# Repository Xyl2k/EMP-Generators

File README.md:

EMP-Generators
==============

Eagle schematics for various basic EMP Generators.

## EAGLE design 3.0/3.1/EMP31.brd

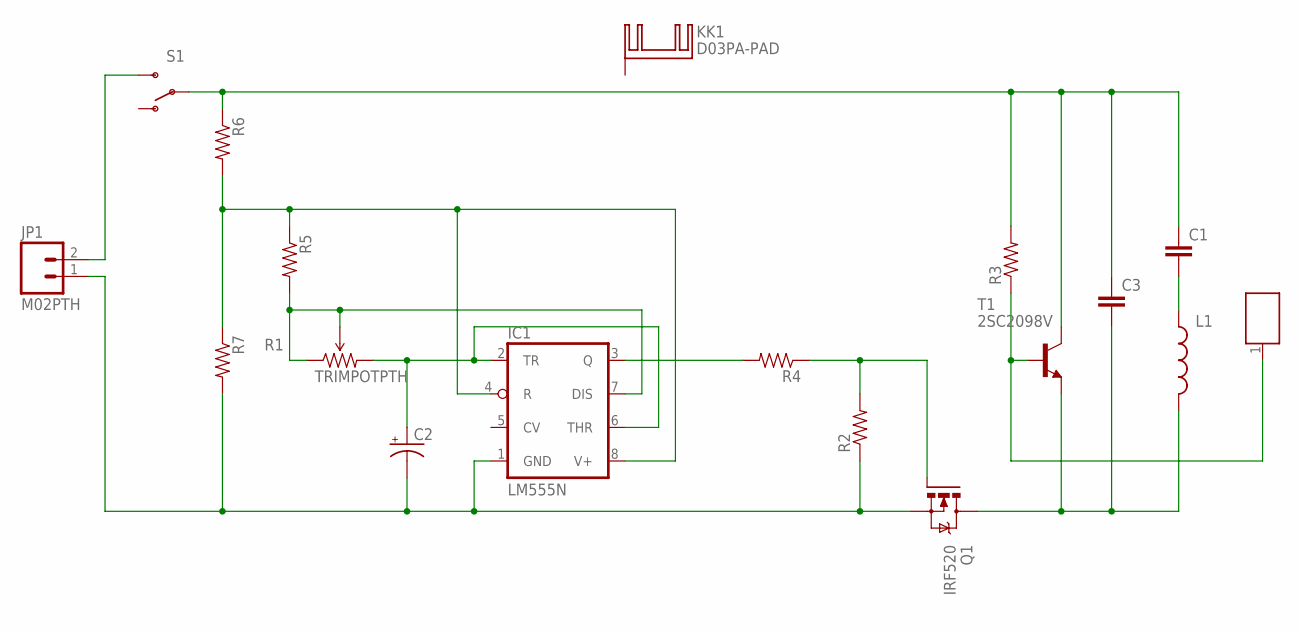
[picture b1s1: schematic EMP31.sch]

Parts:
C1, C3: CAPEZ; CAP-PTH-SMALLEZ
C2: CAP_POLPTH2; CPOL-RADIAL-10UF-25V
IC1: LM555N; DIL08-ROUND
JP1: M02PTH; 1X02
KK1: D03PA-PAD
L1: INDUCTORCR54-KIT; CR54-KIT
Q1: IRF520; TO220BV
R1: TRIMPOTPTH; TRIM_POT_PTH
R2, R3, R4, R5, R6, R7: RESISTOREZ; AXIAL-0.3EZ
S1: SWITCH-SPDTPTH; SWITCH-SPDT
T1: 2SC2098V; TO220AV
U$1: L2_JOB37

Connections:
GND: C2.2 (-), IC1.1 (GND), JP1.1, Q1.S, R2.P$1 (1), R7.P$2 (2)
unnamed: C1.2, L1.P$1 (1)
unnamed: R3.P$1 (1), T1.1 (B), U$1.1
unnamed: C3.2, L1.P$2 (2), Q1.D, T1.3 (E)
unnamed: Q1.G, R2.P$2 (2), R4.P$1 (1)
unnamed: IC1.3 (Q), R4.P$2 (2)
unnamed: C2.1 (+), IC1.2 (TR), IC1.6 (THR), R1.3 (CW)
unnamed: IC1.7 (DIS), R1.1 (CCW), R1.2 (WIPER), R5.P$2 (2)
unnamed: IC1.4 (R), IC1.8 (V+), R5.P$1 (1), R6.P$2 (2), R7.P$1 (1)
unnamed: C1.1, C3.1, R3.P$2 (2), R6.P$1 (1), S1.2, T1.2 (C)
unnamed: JP1.2, S1.3 (S)

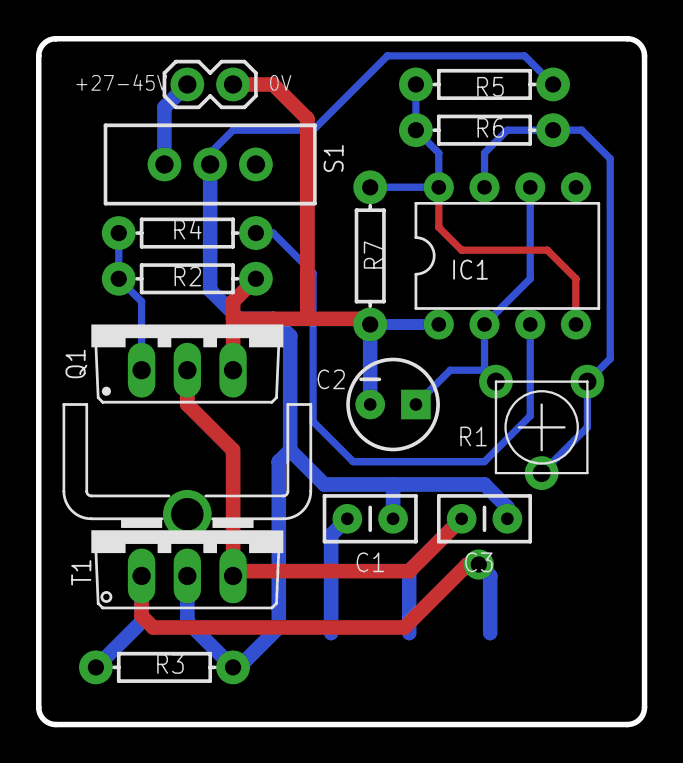
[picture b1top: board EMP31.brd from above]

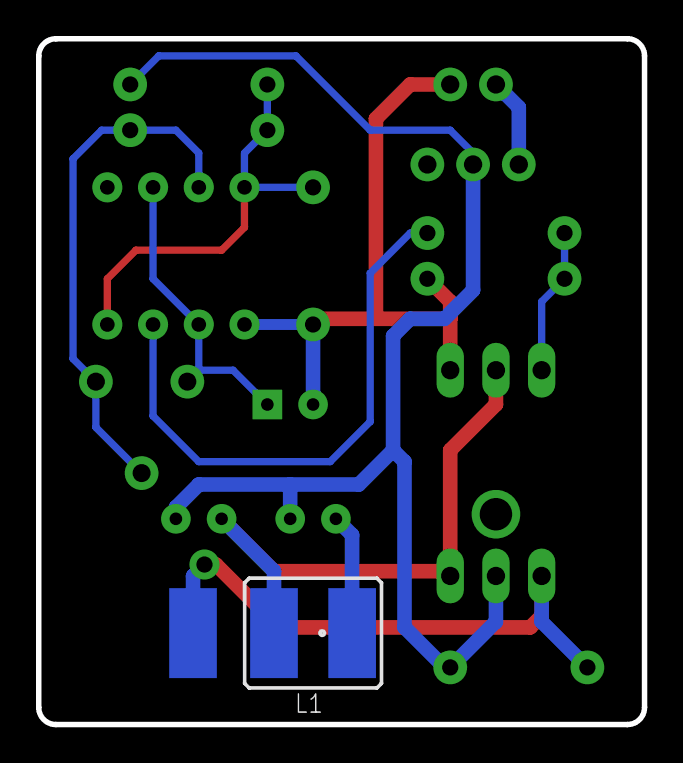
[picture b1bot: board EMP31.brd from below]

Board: 2 copper layers, 33.7 x 38.1 mm, 18 parts (2 on the bottom side), 11 nets.

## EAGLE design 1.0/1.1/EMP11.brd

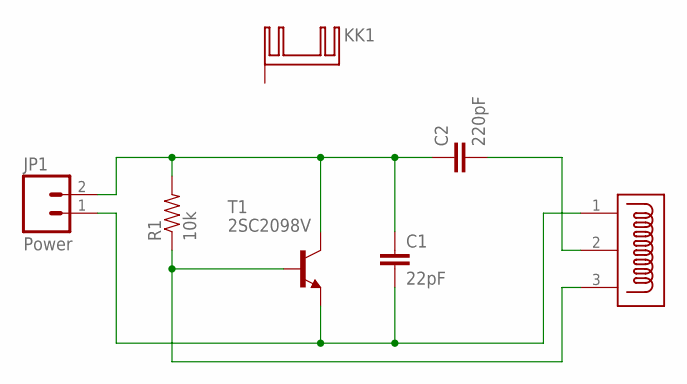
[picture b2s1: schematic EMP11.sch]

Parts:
C1: 22pF; CAP-PTH-SMALL
C2: 220pF; CAP-PTH-SMALL
JP1: Power; 1X02
KK1: D03PA-PAD
R1: 10k; AXIAL-0.4
T1: 2SC2098V; TO220AV
U$1: EMP_WIRE

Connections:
27V: C1.1, C2.1, JP1.2, R1.P$2 (2), T1.2 (C)
GND: C1.2, JP1.1, T1.3 (E), U$1.1
unnamed: R1.P$1 (1), T1.1 (B), U$1.3
unnamed: C2.2, U$1.2

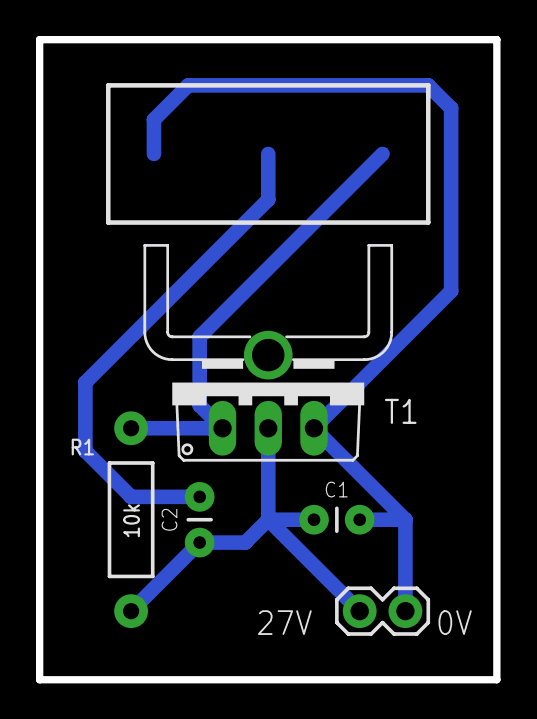
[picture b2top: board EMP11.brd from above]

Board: 2 copper layers, 25.4 x 35.6 mm, 7 parts (0 on the bottom side), 4 nets.

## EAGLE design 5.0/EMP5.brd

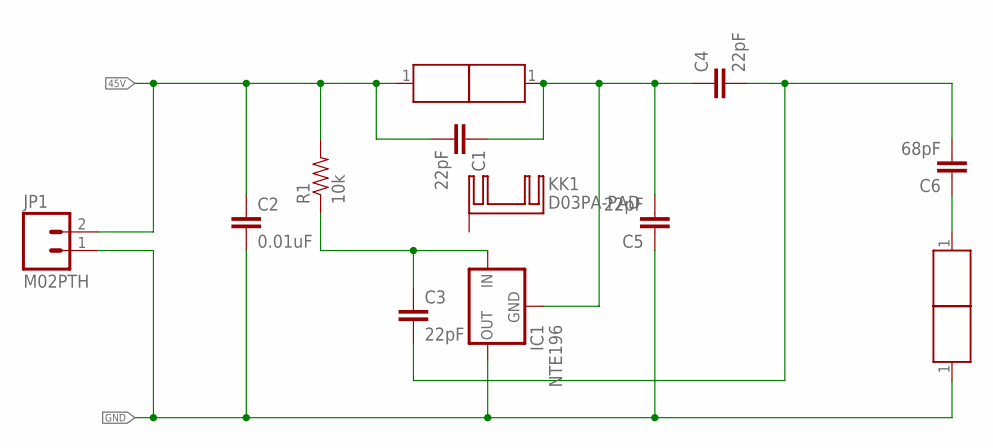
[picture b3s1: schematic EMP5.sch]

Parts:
C1, C3, C4, C5: 22pF; CAP-PTH-SMALL-KIT
C2: 0.01uF; CAP-PTH-SMALL-KIT
C6: 68pF; CAP-PTH-SMALL-KIT
IC1: NTE196; TO220-IGO
JP1: M02PTH; 1X02
KK1: D03PA-PAD
L1-1, L1-2, L2-1, L2-2: L2_JOB37
R1: 10k; AXIAL-0.3EZ

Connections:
45V: C1.2, C2.1, JP1.2, L1-1.1, R1.P$2 (2)
GND: C2.2, C5.1, IC1.OUT, JP1.1, L2-2.1
unnamed: C3.1, IC1.IN, R1.P$1 (1)
unnamed: C1.1, C4.1, C5.2, IC1.GND, L1-2.1
unnamed: C6.1, L2-1.1
unnamed: C3.2, C4.2, C6.2

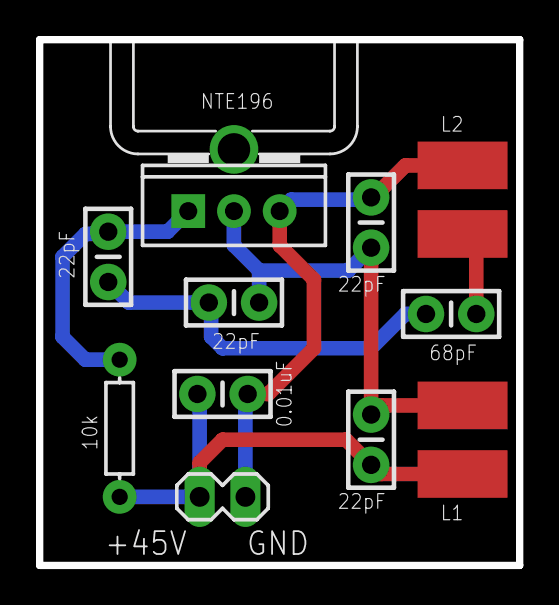
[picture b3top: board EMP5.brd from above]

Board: 2 copper layers, 26.7 x 29.2 mm, 14 parts (0 on the bottom side), 6 nets.

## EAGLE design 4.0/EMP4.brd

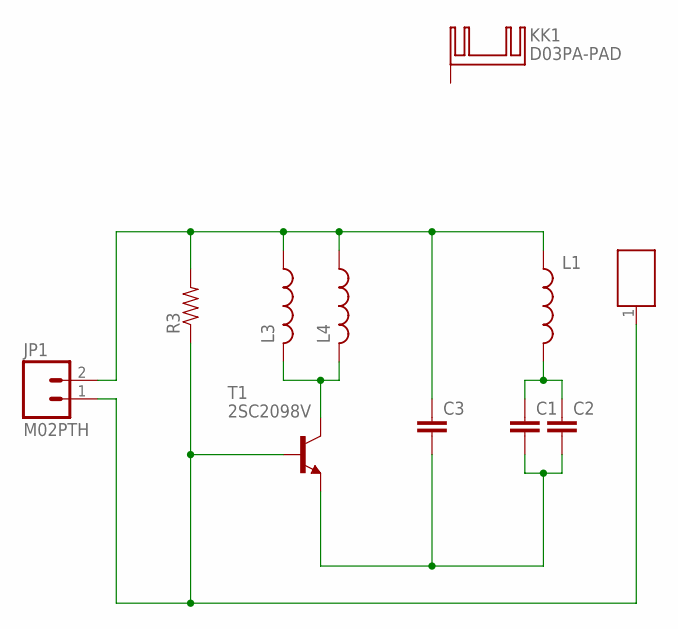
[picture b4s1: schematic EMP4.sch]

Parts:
C1, C2, C3: CAPEZ; CAP-PTH-SMALLEZ
JP1: M02PTH; 1X02
KK1: D03PA-PAD
L1: INDUCTORCR54-KIT; CR54-KIT
L3, L4: L-USTFI0307; TFI0307
R3: RESISTOREZ; AXIAL-0.3EZ
T1: 2SC2098V; TO220AV
U$1: L2_JOB37

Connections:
GND: JP1.1, R3.P$1 (1), T1.1 (B), U$1.1
unnamed: C1.1, C2.1, L1.P$2 (2)
unnamed: C1.2, C2.2, C3.2, T1.3 (E)
unnamed: L3.2, L4.2, T1.2 (C)
VCC: C3.1, JP1.2, L1.P$1 (1), L3.1, L4.1, R3.P$2 (2)

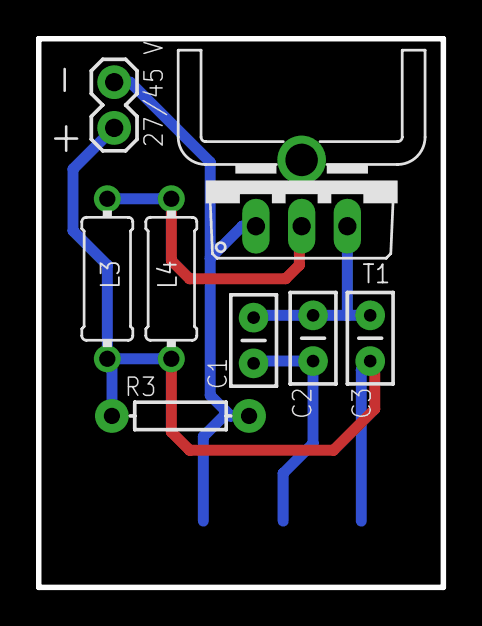
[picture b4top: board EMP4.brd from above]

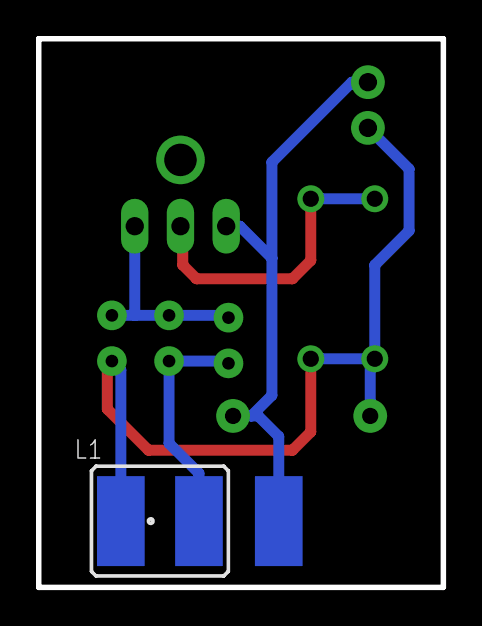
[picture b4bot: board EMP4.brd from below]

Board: 2 copper layers, 22.5 x 30.5 mm, 11 parts (2 on the bottom side), 5 nets.

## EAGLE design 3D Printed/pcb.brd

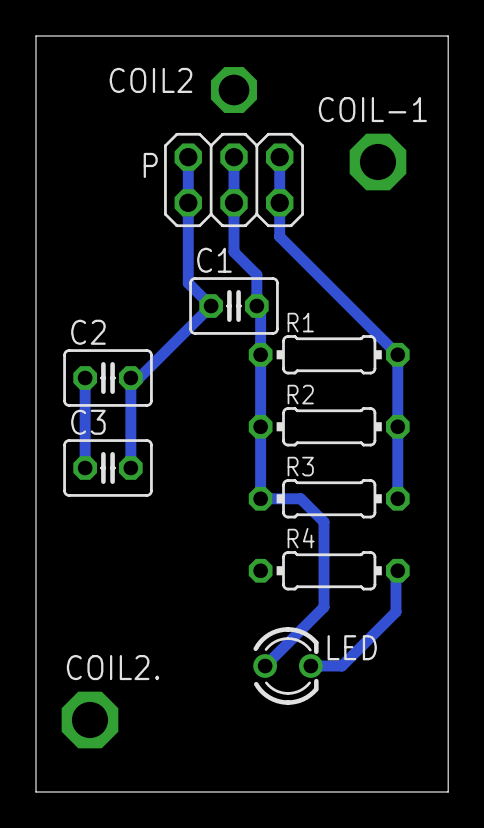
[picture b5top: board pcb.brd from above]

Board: 2 copper layers, 22.9 x 42.0 mm, 12 parts (0 on the bottom side), 5 nets.

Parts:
C1, C2, C3: C025-030X050
COIL2: P1-17
COIL2.: P1-20
COIL-1: P1-20
LED: LED3MM
P: 2X03
R1, R2, R3, R4: 0204/7

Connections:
S$1: COIL-1.TP, P.5, P.6, R1.2, R2.2, R3.2
S$4: C1.2, COIL2.TP, LED.A, P.3, P.4, R1.1, R2.1, R3.1
S$5: LED.K, R4.2
S$6: C2.1, C3.1, COIL2..TP
S$7: C1.1, C2.2, C3.2, P.1, P.2, R4.1

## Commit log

2014-11-23 :boom::camel: Added .gitattributes & .gitignore files
2014-11-23 Eagle schematics
    Eagle schematics
2016-03-22 Added a new version
    https://hackaday.io/project/10464-chinese-emp-generator

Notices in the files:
parts and their libraries:
SparkFun-Capacitors: Licensing: Creative Commons ShareAlike 4.0 International - https://creativecommons.org/licenses/by-sa/4.0
